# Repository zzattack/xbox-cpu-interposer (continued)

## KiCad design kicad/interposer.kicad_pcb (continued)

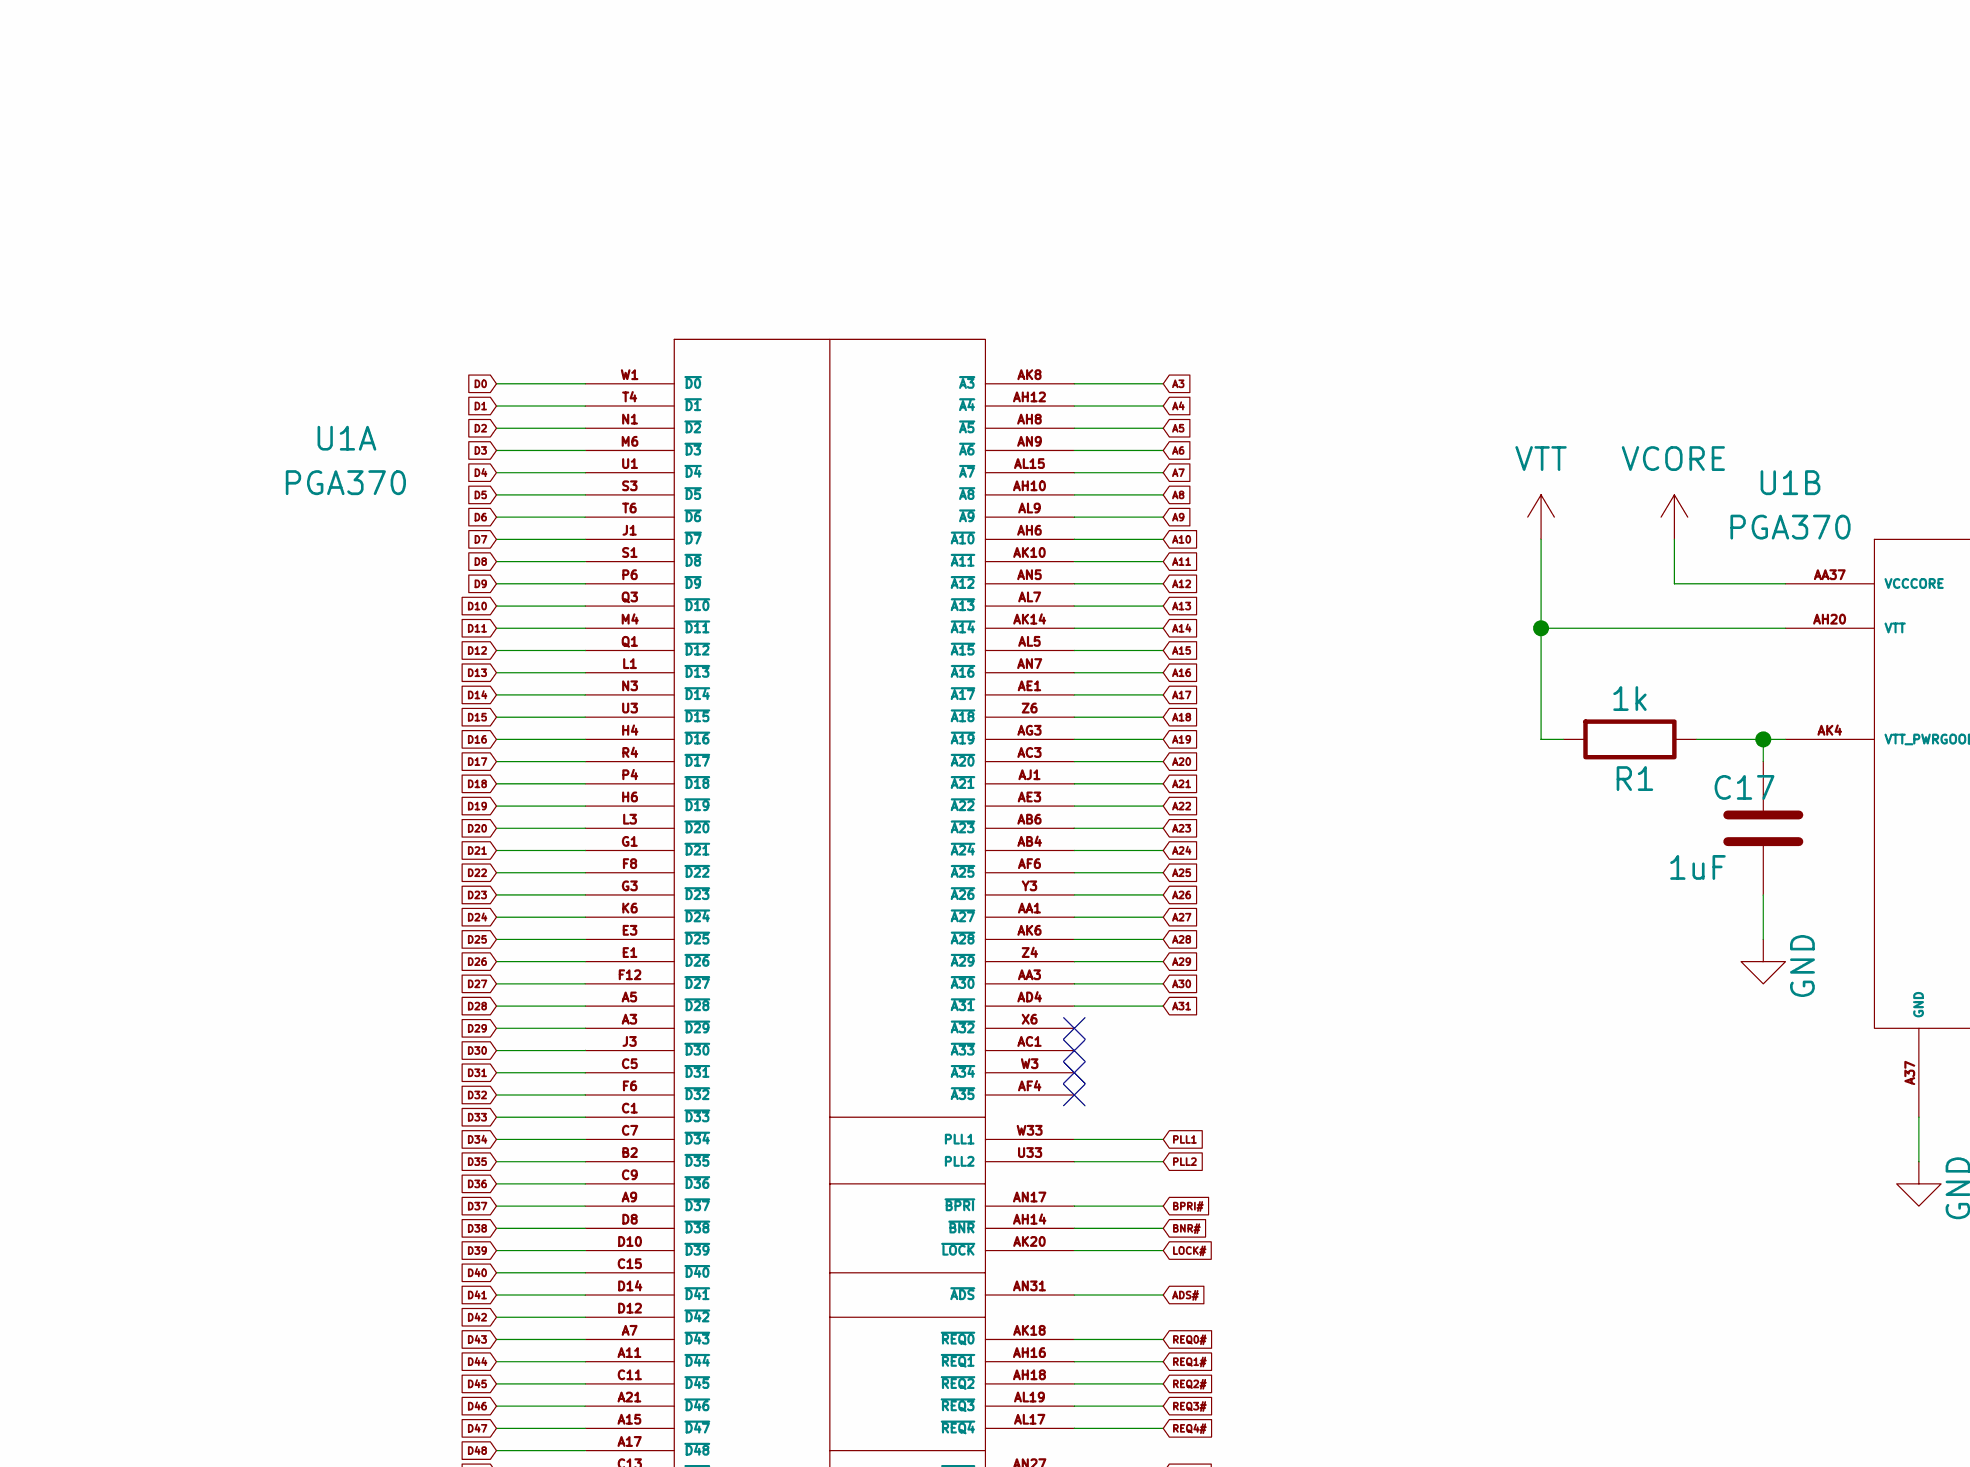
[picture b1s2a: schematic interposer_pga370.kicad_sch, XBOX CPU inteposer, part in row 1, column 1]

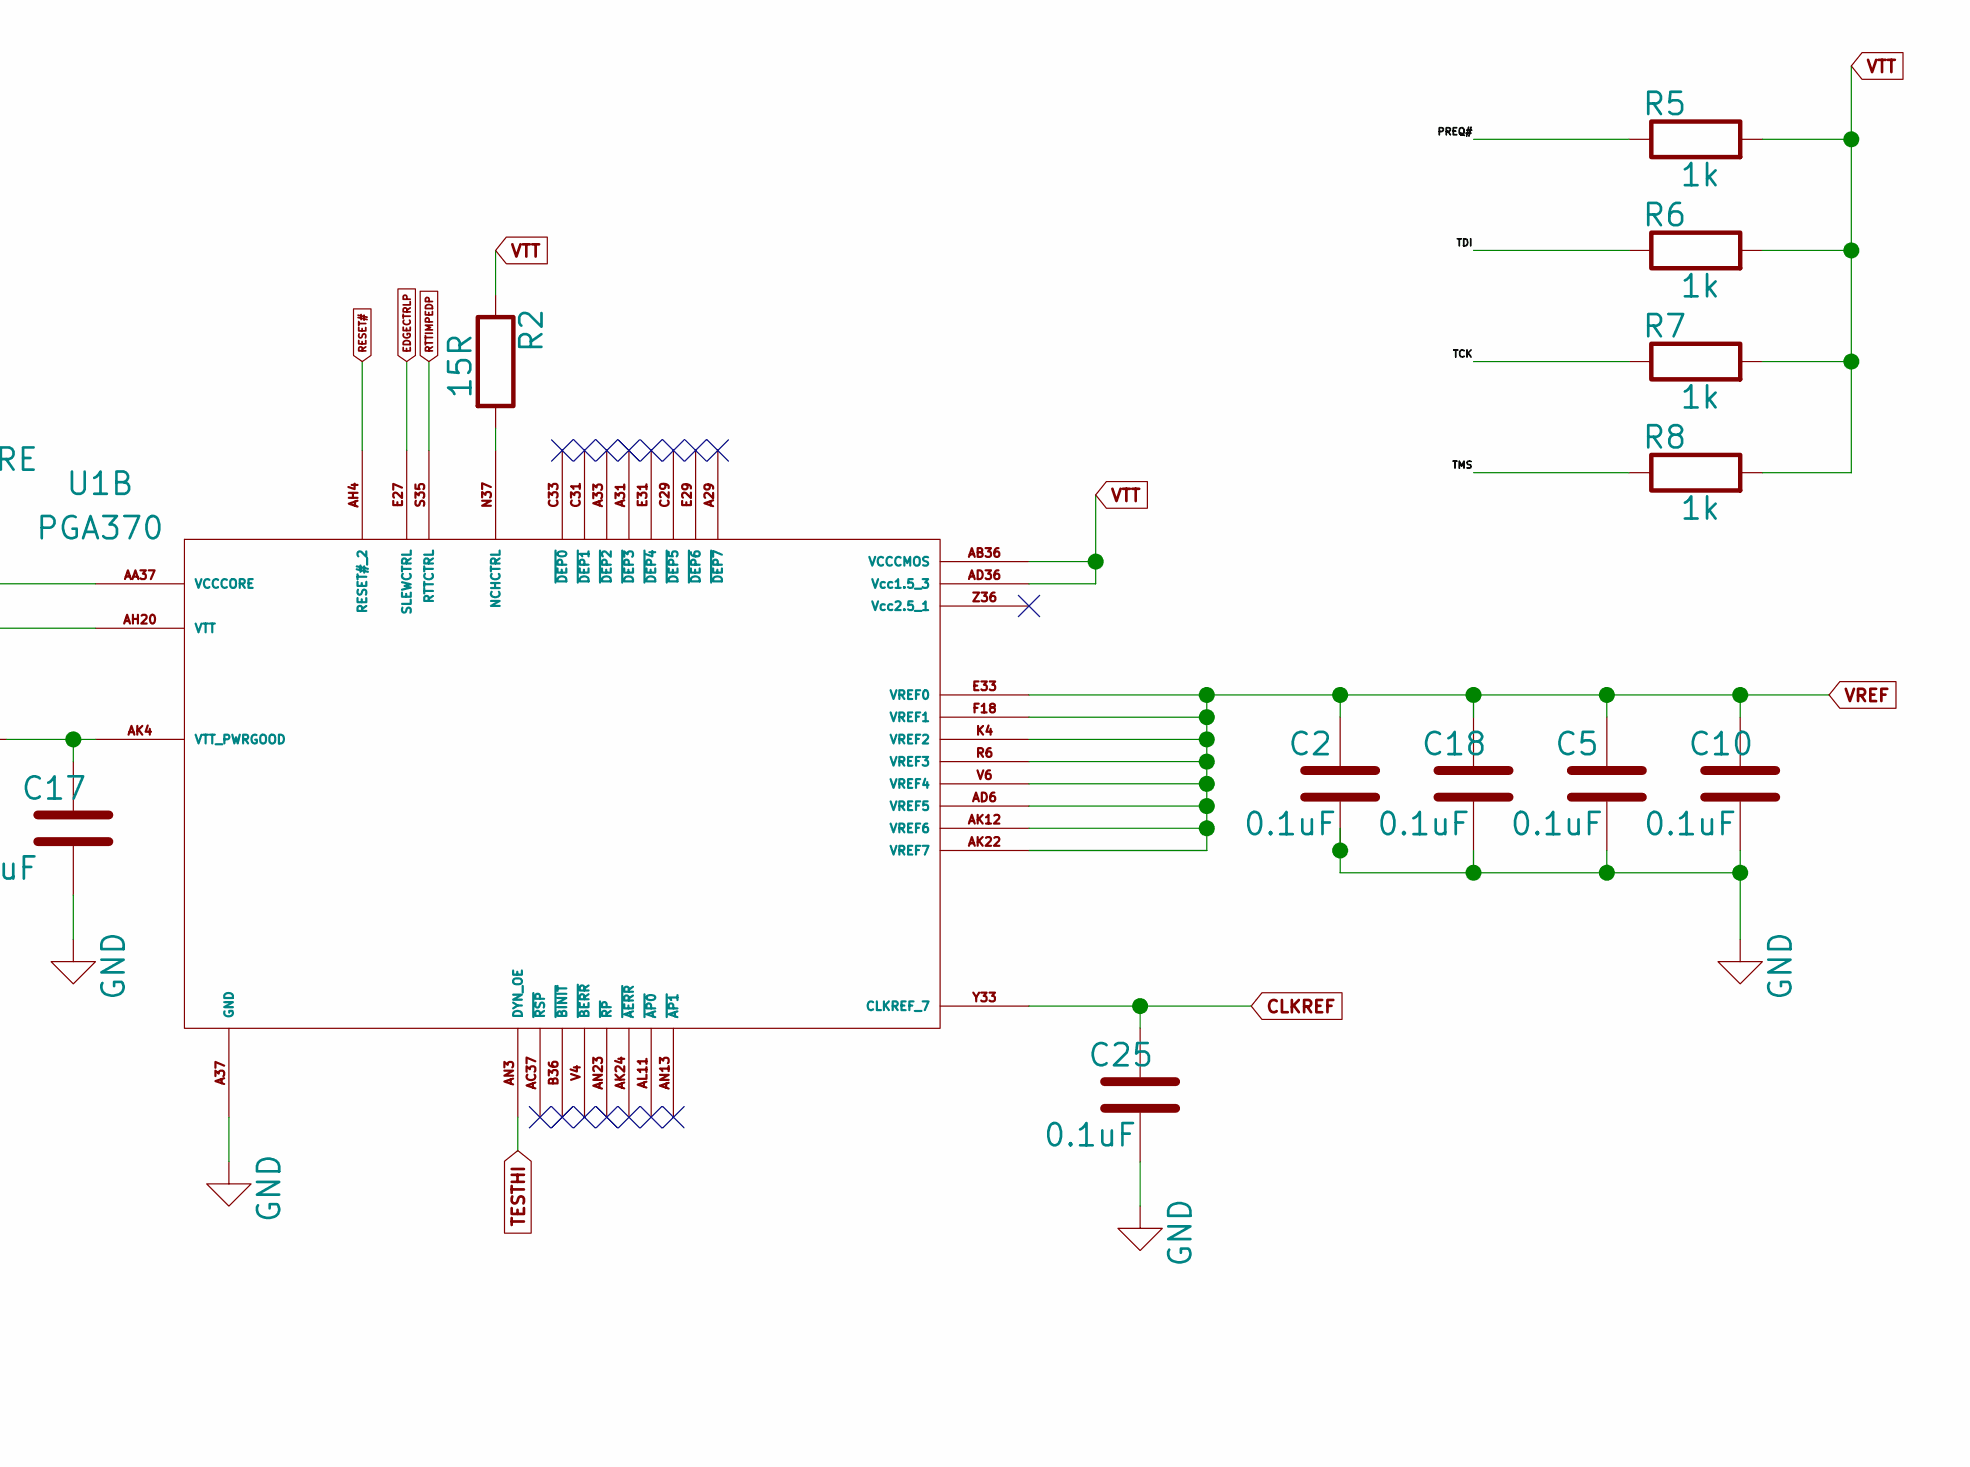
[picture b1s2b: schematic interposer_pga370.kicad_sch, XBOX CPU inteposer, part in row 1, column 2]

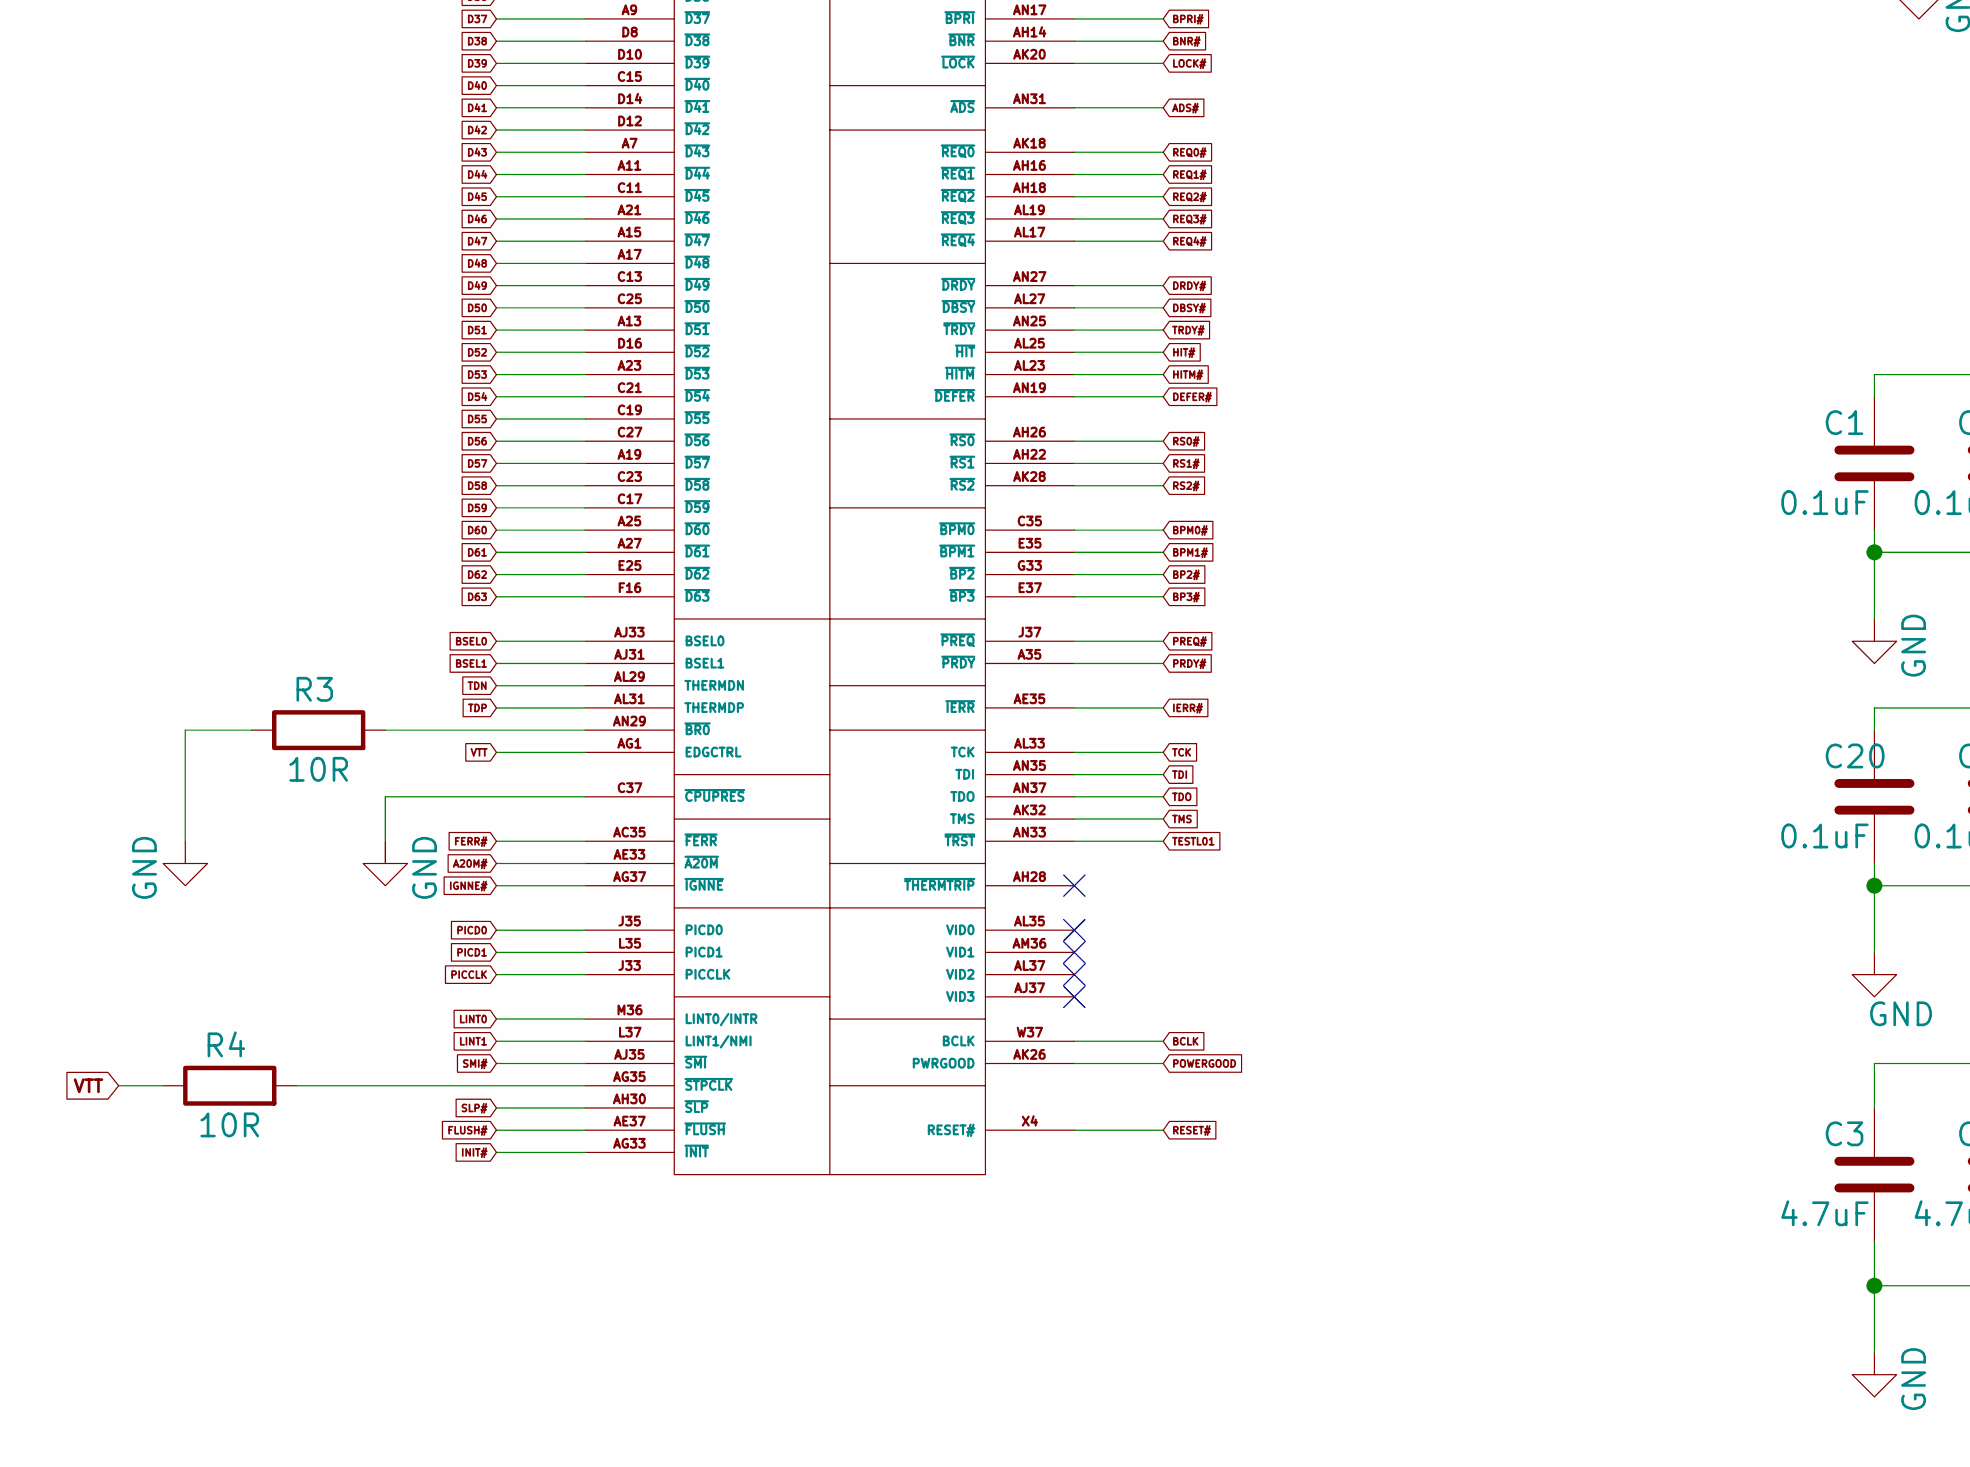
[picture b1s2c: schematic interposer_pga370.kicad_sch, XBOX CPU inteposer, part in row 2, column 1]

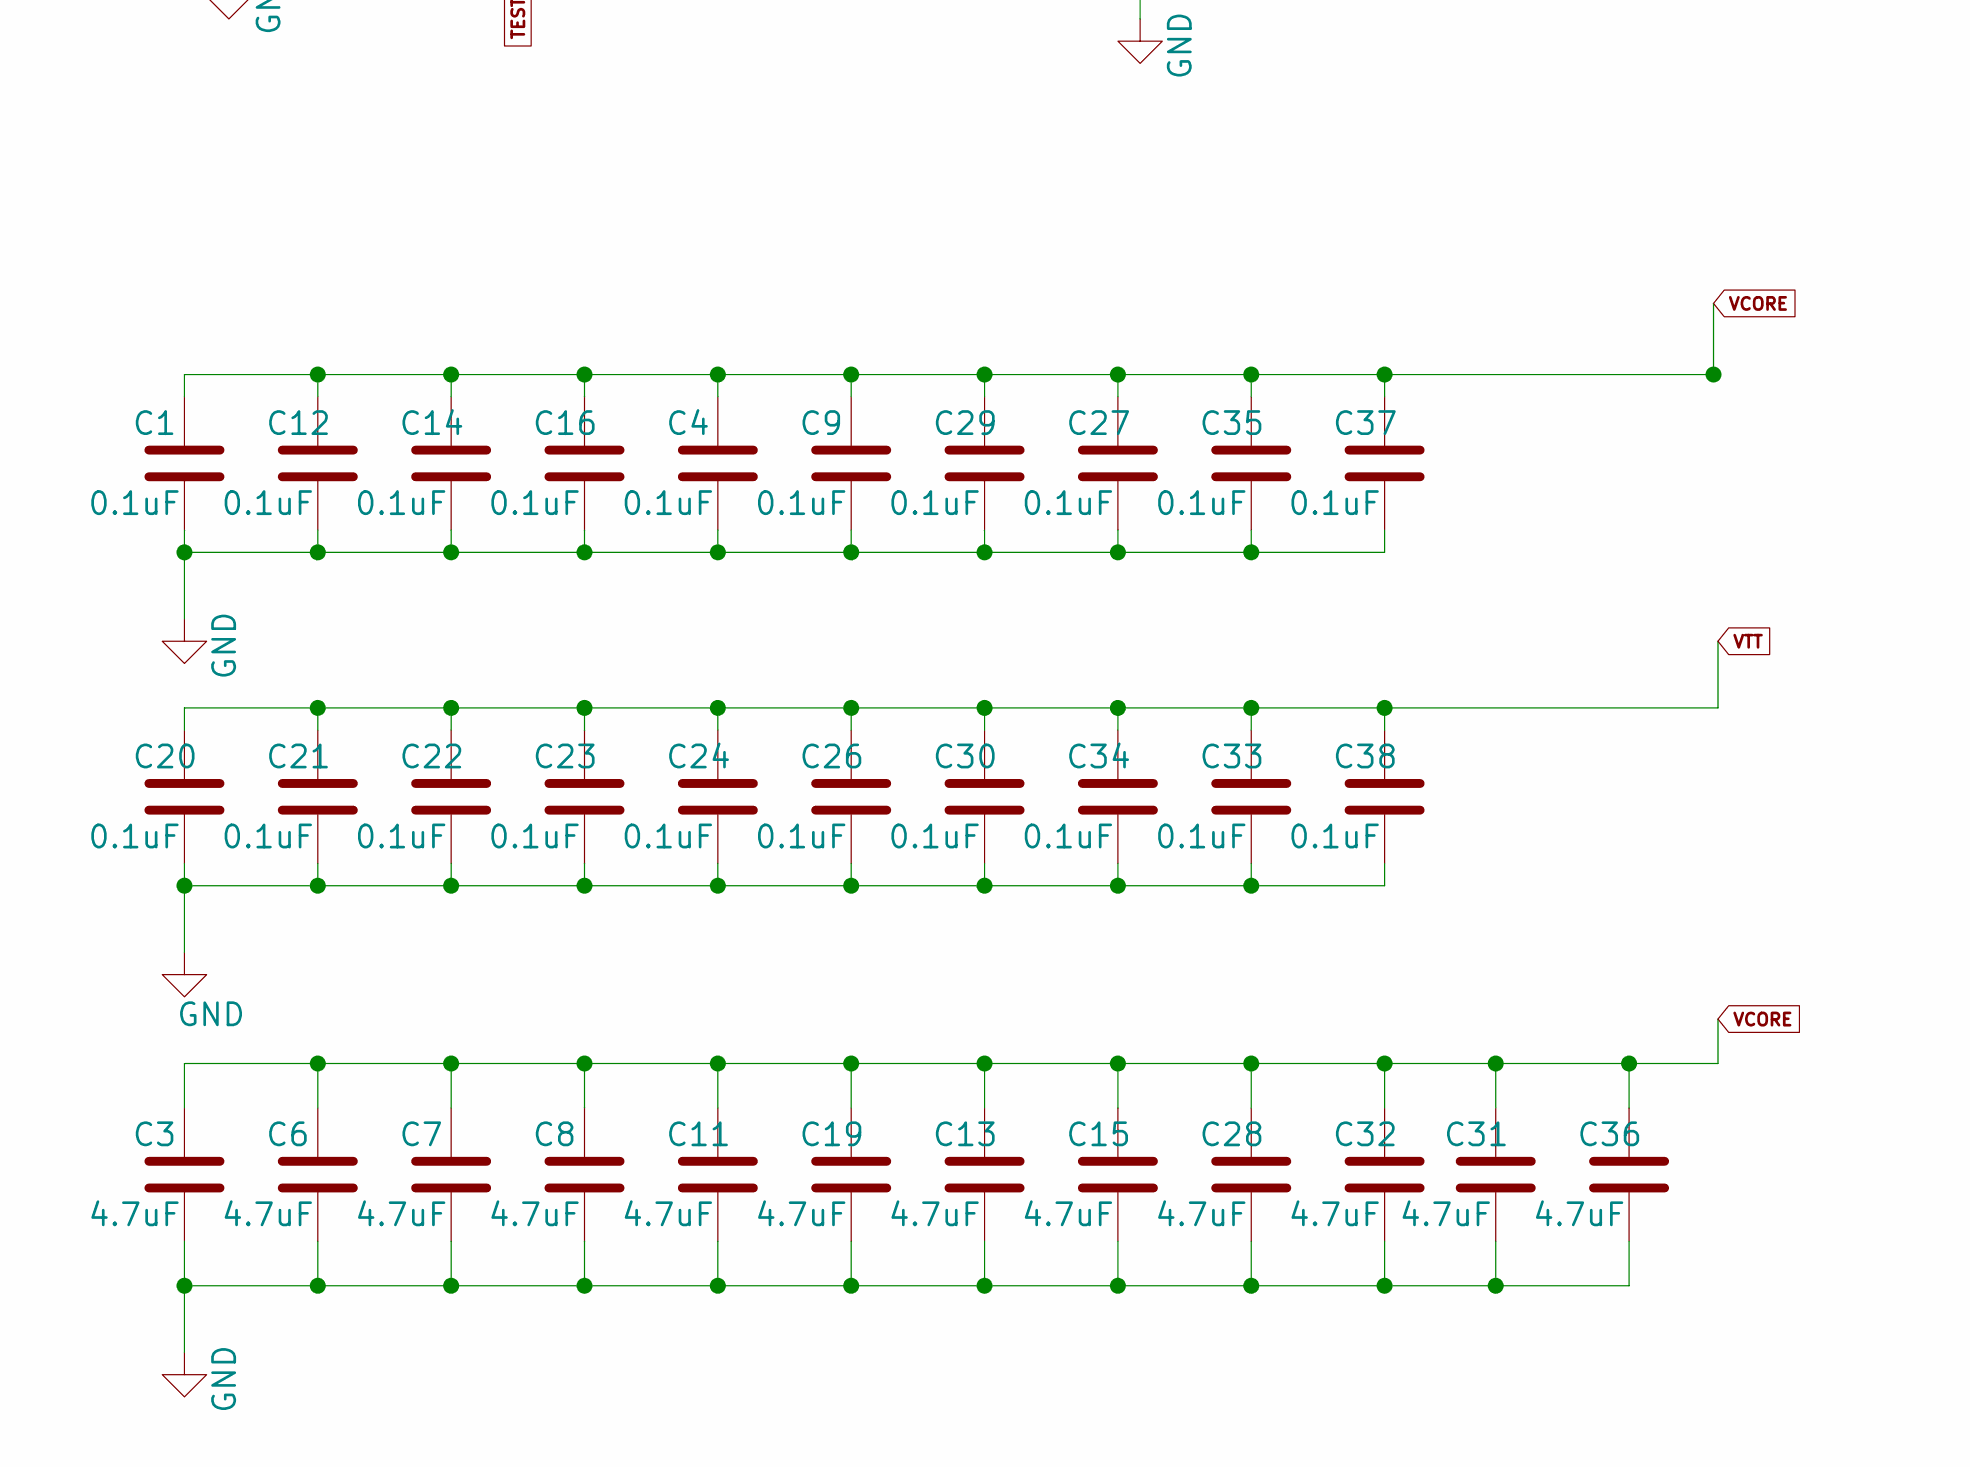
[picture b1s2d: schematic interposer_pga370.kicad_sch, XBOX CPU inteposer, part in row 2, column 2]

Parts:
C1, C2, C4, C5, C9, C10, C12, C14, C16, C18, C20, C21, C22, C23, C24, C25, C26, C27, C29, C30, C33, C34, C35, C37, C38: 0.1uF; C_0603_1608Metric
C3, C6, C7, C8, C11, C13, C15, C19, C28, C31, C32, C36: 4.7uF; C_0805_2012Metric
C17: 1uF; C_0603_1608Metric
R1, R5, R6, R7, R8: 1k; R_0603_1608Metric
R2: 15R; R_0603_1608Metric
R3, R4: 10R; R_0603_1608Metric
U1: PGA370

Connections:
A3: U1.AK8 (~A3); also elsewhere on the board
A4: U1.AH12 (~A4); also elsewhere on the board
A5: U1.AH8 (~A5); also elsewhere on the board
A6: U1.AN9 (~A6); also elsewhere on the board
A7: U1.AL15 (~A7); also elsewhere on the board
A8: U1.AH10 (~A8); also elsewhere on the board
A9: U1.AL9 (~A9); also elsewhere on the board
A10: U1.AH6 (~A10); also elsewhere on the board
A11: U1.AK10 (~A11); also elsewhere on the board
A12: U1.AN5 (~A12); also elsewhere on the board
A13: U1.AL7 (~A13); also elsewhere on the board
A14: U1.AK14 (~A14); also elsewhere on the board
A15: U1.AL5 (~A15); also elsewhere on the board
A16: U1.AN7 (~A16); also elsewhere on the board
A17: U1.AE1 (~A17); also elsewhere on the board
A18: U1.Z6 (~A18); also elsewhere on the board
A19: U1.AG3 (~A19); also elsewhere on the board
A20: U1.AC3 (~A20); also elsewhere on the board
A20M#: U1.AE33 (~A20M); also elsewhere on the board
A21: U1.AJ1 (~A21); also elsewhere on the board
A22: U1.AE3 (~A22); also elsewhere on the board
A23: U1.AB6 (~A23); also elsewhere on the board
A24: U1.AB4 (~A24); also elsewhere on the board
A25: U1.AF6 (~A25); also elsewhere on the board
A26: U1.Y3 (~A26); also elsewhere on the board
A27: U1.AA1 (~A27); also elsewhere on the board
A28: U1.AK6 (~A28); also elsewhere on the board
A29: U1.Z4 (~A29); also elsewhere on the board
A30: U1.AA3 (~A30); also elsewhere on the board
A31: U1.AD4 (~A31); also elsewhere on the board
ADS#: U1.AN31 (~ADS); also elsewhere on the board
BCLK: U1.W37 (BCLK); also elsewhere on the board
BNR#: U1.AH14 (~BNR); also elsewhere on the board
BP2#: U1.G33 (~BP2); also elsewhere on the board
BP3#: U1.E37 (~BP3); also elsewhere on the board
BPM0#: U1.C35 (~BPM0); also elsewhere on the board
BPM1#: U1.E35 (~BPM1); also elsewhere on the board
BPRI#: U1.AN17 (~BPRI); also elsewhere on the board
BSEL0: U1.AJ33 (BSEL0); also elsewhere on the board
BSEL1: U1.AJ31 (BSEL1); also elsewhere on the board
CLKREF: C25.1, U1.Y33 (CLKREF_7); also elsewhere on the board
D0: U1.W1 (~D0); also elsewhere on the board
D1: U1.T4 (~D1); also elsewhere on the board
D2: U1.N1 (~D2); also elsewhere on the board
D3: U1.M6 (~D3); also elsewhere on the board
D4: U1.U1 (~D4); also elsewhere on the board
D5: U1.S3 (~D5); also elsewhere on the board
D6: U1.T6 (~D6); also elsewhere on the board
D7: U1.J1 (~D7); also elsewhere on the board
D8: U1.S1 (~D8); also elsewhere on the board
D9: U1.P6 (~D9); also elsewhere on the board
D10: U1.Q3 (~D10); also elsewhere on the board
D11: U1.M4 (~D11); also elsewhere on the board
D12: U1.Q1 (~D12); also elsewhere on the board
D13: U1.L1 (~D13); also elsewhere on the board
D14: U1.N3 (~D14); also elsewhere on the board
D15: U1.U3 (~D15); also elsewhere on the board
D16: U1.H4 (~D16); also elsewhere on the board
D17: U1.R4 (~D17); also elsewhere on the board
D18: U1.P4 (~D18); also elsewhere on the board
D19: U1.H6 (~D19); also elsewhere on the board
D20: U1.L3 (~D20); also elsewhere on the board
D21: U1.G1 (~D21); also elsewhere on the board
D22: U1.F8 (~D22); also elsewhere on the board
D23: U1.G3 (~D23); also elsewhere on the board
D24: U1.K6 (~D24); also elsewhere on the board
D25: U1.E3 (~D25); also elsewhere on the board
D26: U1.E1 (~D26); also elsewhere on the board
D27: U1.F12 (~D27); also elsewhere on the board
D28: U1.A5 (~D28); also elsewhere on the board
D29: U1.A3 (~D29); also elsewhere on the board
D30: U1.J3 (~D30); also elsewhere on the board
D31: U1.C5 (~D31); also elsewhere on the board
D32: U1.F6 (~D32); also elsewhere on the board
D33: U1.C1 (~D33); also elsewhere on the board
D34: U1.C7 (~D34); also elsewhere on the board
D35: U1.B2 (~D35); also elsewhere on the board
D36: U1.C9 (~D36); also elsewhere on the board
D37: U1.A9 (~D37); also elsewhere on the board
D38: U1.D8 (~D38); also elsewhere on the board
D39: U1.D10 (~D39); also elsewhere on the board
D40: U1.C15 (~D40); also elsewhere on the board
D41: U1.D14 (~D41); also elsewhere on the board
D42: U1.D12 (~D42); also elsewhere on the board
D43: U1.A7 (~D43); also elsewhere on the board
D44: U1.A11 (~D44); also elsewhere on the board
D45: U1.C11 (~D45); also elsewhere on the board
D46: U1.A21 (~D46); also elsewhere on the board
D47: U1.A15 (~D47); also elsewhere on the board
D48: U1.A17 (~D48); also elsewhere on the board
D49: U1.C13 (~D49); also elsewhere on the board
D50: U1.C25 (~D50); also elsewhere on the board
D51: U1.A13 (~D51); also elsewhere on the board
D52: U1.D16 (~D52); also elsewhere on the board
D53: U1.A23 (~D53); also elsewhere on the board
D54: U1.C21 (~D54); also elsewhere on the board
D55: U1.C19 (~D55); also elsewhere on the board
D56: U1.C27 (~D56); also elsewhere on the board
D57: U1.A19 (~D57); also elsewhere on the board
D58: U1.C23 (~D58); also elsewhere on the board
D59: U1.C17 (~D59); also elsewhere on the board
D60: U1.A25 (~D60); also elsewhere on the board
D61: U1.A27 (~D61); also elsewhere on the board
D62: U1.E25 (~D62); also elsewhere on the board
D63: U1.F16 (~D63); also elsewhere on the board
DBSY#: U1.AL27 (~DBSY); also elsewhere on the board
DEFER#: U1.AN19 (~DEFER); also elsewhere on the board
DRDY#: U1.AN27 (~DRDY); also elsewhere on the board
EDGECTRLP: U1.E27 (SLEWCTRL); also elsewhere on the board
FERR#: U1.AC35 (~FERR); also elsewhere on the board
FLUSH#: U1.AE37 (~FLUSH); also elsewhere on the board
GND: C1.2, C2.2, C3.2, C4.2, C5.2, C6.2, C7.2, C8.2, C9.2, C10.2, C11.2, C12.2, C13.2, C14.2, C15.2, C16.2, C17.2, C18.2, C19.2, C20.2, C21.2, C22.2, C23.2, C24.2, C25.2, C26.2, C27.2, C28.2, C29.2, C30.2, C31.2, C32.2, C33.2, C34.2, C35.2, C36.2, C37.2, C38.2, R3.1, U1.A37 (GND), U1.AB32 (GND), U1.AC5 (GND), U1.AC33 (GND), U1.AD2 (GND), U1.AD34 (GND), U1.AF32 (GND), U1.AG5 (GND), U1.AH2 (GND), U1.AH34 (GND), U1.AJ7 (GND), U1.AJ11 (GND), U1.AJ15 (GND), U1.AJ19 (GND), U1.AJ23 (GND), U1.AJ27 (GND), U1.AL3 (GND), U1.AM6 (GND), U1.AM10 (GND), U1.AM14 (GND), U1.AM18 (GND), U1.AM22 (GND), U1.AM26 (GND), U1.AM30 (GND), U1.AM34 (GND), U1.B4 (GND), U1.B8 (GND), U1.B12 (GND), U1.B16 (GND), U1.B20 (GND), U1.B24 (GND), U1.B28 (GND), U1.B32 (GND), U1.C37 (~CPUPRES), U1.D2 (GND), U1.D4 (GND), U1.D18 (GND), U1.D22 (GND), U1.D26 (GND), U1.D30 (GND), U1.D34 (GND), U1.E7 (GND), U1.E11 (GND), U1.E15 (GND), U1.E19 (GND), U1.F20 (GND), U1.F24 (GND), U1.F28 (GND), U1.F32 (GND), U1.F36 (GND), U1.G5 (GND), U1.H2 (GND), U1.H34 (GND), U1.K36 (GND), U1.L5 (GND), U1.M2 (GND), U1.M34 (GND), U1.P32 (GND), U1.P36 (GND), U1.Q5 (GND), U1.R34 (GND), U1.T32 (GND), U1.T36 (GND), U1.U5 (GND), U1.V2 (GND), U1.V34 (GND), U1.X32 (GND), U1.X36 (GND), U1.Y5 (GND), U1.Y37 (GND), U1.Z2 (GND), U1.Z34 (GND); also elsewhere on the board
HIT#: U1.AL25 (~HIT); also elsewhere on the board
HITM#: U1.AL23 (~HITM); also elsewhere on the board
IERR#: U1.AE35 (~IERR); also elsewhere on the board
IGNNE#: U1.AG37 (~IGNNE); also elsewhere on the board
INIT#: U1.AG33 (~INIT); also elsewhere on the board
LINT0: U1.M36 (LINT0/INTR); also elsewhere on the board
LINT1: U1.L37 (LINT1/NMI); also elsewhere on the board
LOCK#: U1.AK20 (~LOCK); also elsewhere on the board
unnamed: R3.2, U1.AN29 (~BR0)
unnamed: R4.2, U1.AG35 (~STPCLK)
unnamed: R2.2, U1.N37 (NCHCTRL)
unnamed: C17.1, R1.1, U1.AK4 (VTT_PWRGOOD)
PICCLK: U1.J33 (PICCLK); also elsewhere on the board
PICD0: U1.J35 (PICD0); also elsewhere on the board
PICD1: U1.L35 (PICD1); also elsewhere on the board
PLL1: U1.W33 (PLL1); also elsewhere on the board
PLL2: U1.U33 (PLL2); also elsewhere on the board
POWERGOOD: U1.AK26 (PWRGOOD); also elsewhere on the board
PRDY#: U1.A35 (~PRDY); also elsewhere on the board
PREQ#: R5.1, U1.J37 (~PREQ)
REQ0#: U1.AK18 (~REQ0); also elsewhere on the board
REQ1#: U1.AH16 (~REQ1); also elsewhere on the board
REQ2#: U1.AH18 (~REQ2); also elsewhere on the board
REQ3#: U1.AL19 (~REQ3); also elsewhere on the board
REQ4#: U1.AL17 (~REQ4); also elsewhere on the board
RESET#: U1.AH4 (RESET#_2), U1.X4 (RESET#); also elsewhere on the board
RS0#: U1.AH26 (~RS0); also elsewhere on the board
RS1#: U1.AH22 (~RS1); also elsewhere on the board
RS2#: U1.AK28 (~RS2); also elsewhere on the board
RTTIMPEDP: U1.S35 (RTTCTRL); also elsewhere on the board
SLP#: U1.AH30 (~SLP); also elsewhere on the board
SMI#: U1.AJ35 (~SMI); also elsewhere on the board
TCK: R7.1, U1.AL33 (TCK)
TDI: R6.1, U1.AN35 (TDI)
TDN: U1.AL29 (THERMDN); also elsewhere on the board
TDO: U1.AN37 (TDO); also elsewhere on the board
TDP: U1.AL31 (THERMDP); also elsewhere on the board
TESTHI: U1.AN3 (DYN_OE); also elsewhere on the board
TESTL01: U1.AN33 (~TRST); also elsewhere on the board
TMS: R8.1, U1.AK32 (TMS)
TRDY#: U1.AN25 (~TRDY); also elsewhere on the board
VCORE: C1.1, C3.1, C4.1, C6.1, C7.1, C8.1, C9.1, C11.1, C12.1, C13.1, C14.1, C15.1, C16.1, C19.1, C27.1, C28.1, C29.1, C31.1, C32.1, C35.1, C36.1, C37.1, U1.AA5 (VCORE), U1.AA37 (VCCCORE), U1.AB2 (VCORE), U1.AB34 (VCORE), U1.AD32 (VCORE), U1.AE5 (VCORE), U1.AF2 (VCORE), U1.AF34 (VCORE), U1.AH24 (VCORE), U1.AH32 (VCORE), U1.AH36 (VCORE), U1.AJ5 (VCORE), U1.AJ9 (VCORE), U1.AJ13 (VCORE), U1.AJ17 (VCORE), U1.AJ21 (VCORE), U1.AJ25 (VCORE), U1.AJ29 (VCORE), U1.AK2 (VCORE), U1.AK34 (VCORE), U1.AM4 (VCORE), U1.AM8 (VCORE), U1.AM12 (VCORE), U1.AM16 (VCORE), U1.AM20 (VCORE), U1.AM24 (VCORE), U1.AM28 (VCORE), U1.AM32 (VCORE), U1.B6 (VCORE), U1.B10 (VCORE), U1.B14 (VCORE), U1.B18 (VCORE), U1.B22 (VCORE), U1.B26 (VCORE), U1.B30 (VCORE), U1.B34 (VCORE), U1.C3 (VCORE), U1.D6 (VCORE), U1.D20 (VCORE), U1.D24 (VCORE), U1.D28 (VCORE), U1.D32 (VCORE), U1.D36 (VCORE), U1.E5 (VCORE), U1.E9 (VCORE), U1.E13 (VCORE), U1.E17 (VCORE), U1.F2 (VCORE), U1.F4 (VCORE), U1.F14 (VCORE), U1.F22 (VCORE), U1.F26 (VCORE), U1.F30 (VCORE), U1.F34 (VCORE), U1.H32 (VCORE), U1.H36 (VCORE), U1.J5 (VCORE), U1.K2 (VCORE), U1.K32 (VCORE), U1.K34 (VCORE), U1.M32 (VCORE), U1.N5 (VCORE), U1.P2 (VCORE), U1.P34 (VCORE), U1.R32 (VCORE), U1.R36 (VCORE), U1.S5 (VCORE), U1.T2 (VCORE), U1.T34 (VCORE), U1.V32 (VCORE), U1.V36 (VCORE), U1.W5 (VCORE), U1.Y35 (VCORE), U1.Z32 (VCORE); also elsewhere on the board
VREF: C2.1, C5.1, C10.1, C18.1, U1.AD6 (VREF5), U1.AK12 (VREF6), U1.AK22 (VREF7), U1.E33 (VREF0), U1.F18 (VREF1), U1.K4 (VREF2), U1.R6 (VREF3), U1.V6 (VREF4); also elsewhere on the board
VTT: C20.1, C21.1, C22.1, C23.1, C24.1, C26.1, C30.1, C33.1, C34.1, C38.1, R1.2, R2.1, R4.1, R5.2, R6.2, R7.2, R8.2, U1.AA33 (VTT), U1.AA35 (VTT), U1.AB36 (VCCCMOS), U1.AD36 (Vcc1.5_3), U1.AG1 (EDGCTRL), U1.AH20 (VTT), U1.AK16 (VTT), U1.AL13 (VTT), U1.AL21 (VTT), U1.AN11 (VTT), U1.AN15 (VTT), U1.AN21 (VTT), U1.E23 (VTT), U1.G35 (VTT), U1.G37 (VTT), U1.S33 (VTT), U1.S37 (VTT), U1.U35 (VTT), U1.U37 (VTT), U1.X34 (VTT); also elsewhere on the board

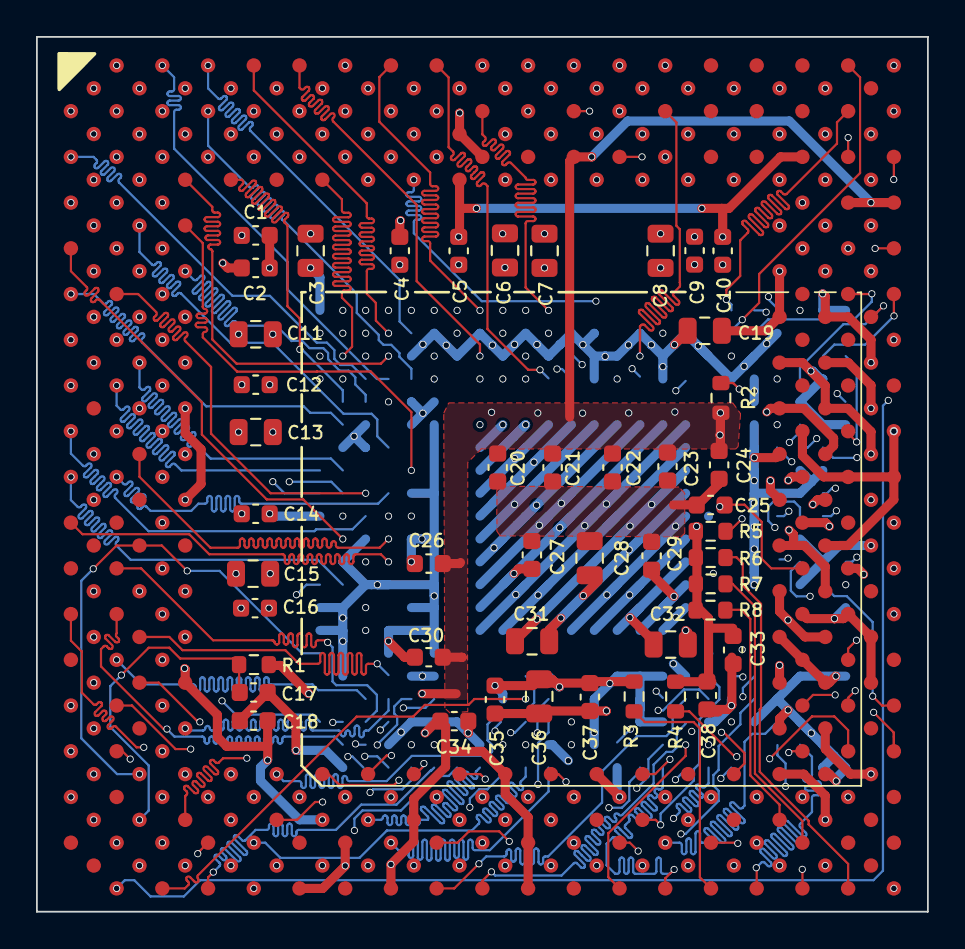
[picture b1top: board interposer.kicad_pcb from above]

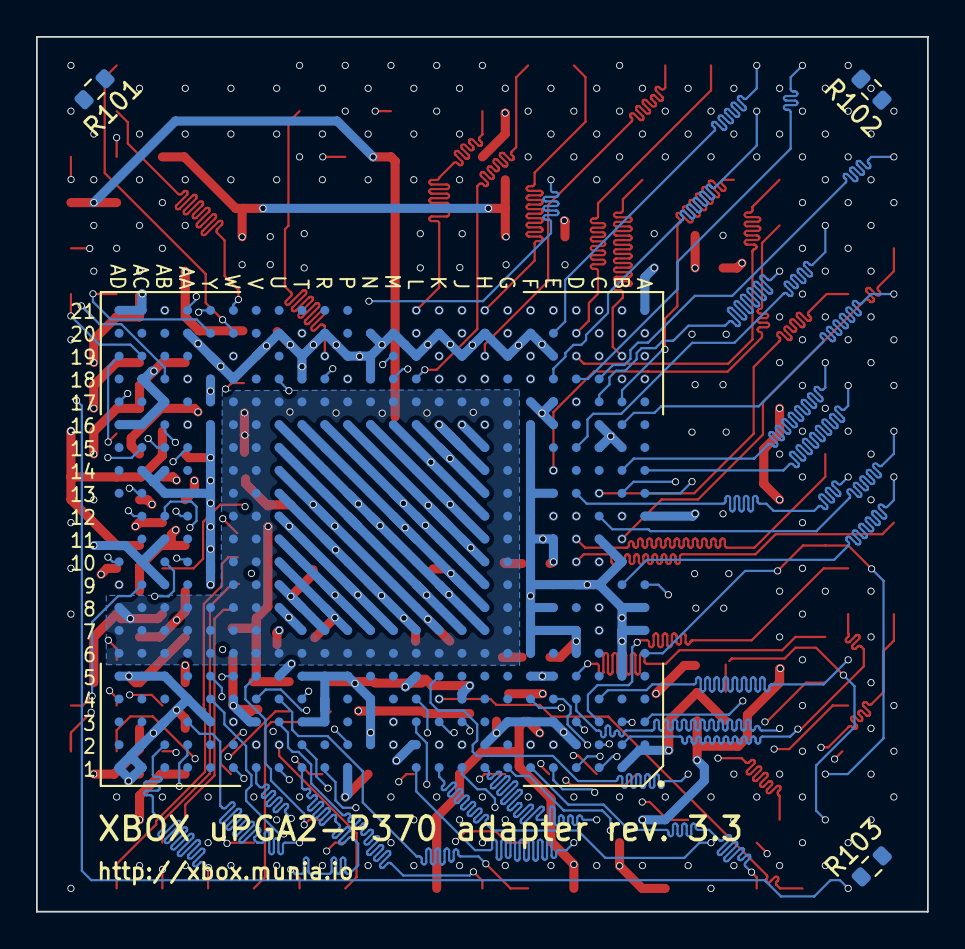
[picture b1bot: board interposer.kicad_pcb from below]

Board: 6 copper layers, 49.5 x 48.6 mm, 51 parts (4 on the bottom side), 156 nets.

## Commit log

2023-11-26 Add aligned and cleaned-up scans of delayered board
2023-11-26 Add datasheets for the source and target processor families
2023-11-26 Add kicad project with sch, symbols, footprints and pcb
2023-11-26 Add friendtech patent
2023-11-28 Reroute with BGA more centered and cheaper design fabrications (0.3mm drills).
2023-11-28 Remove license
2023-11-29 Optimizations: - remove via's out of silk screen text - eliminate warnings - tighter board outline
2023-12-01 Revision 3; much cleaner layout with traces tuned to 25mm.
2023-12-01 Add tool to help with alignment of the board
2023-12-01 Add gerbers for aligntool
2023-12-08 Rev 3.1: - change via's to 0.3mm drill/0.4mm ring for cheaper manufacturing - add leveling 0603 resistors on backside in the corners to prevent PCB tilt during reflow
2024-01-07 Revision 3.2
    Implement fixes that allow interposer to be actually functional for the first time:
    - Fix uBGA495 pin P1 from VTT --> VCC since this is VCC on xbox motherboard.
    - Fix P370 pin AJ3 (RESET2#) from GND --> NC.
    Furthermore, pins AL1 (reserved), AK36 (VID output), AF36 (DETECT) now left NC instead of connected to GND.
    Outline slightly trimmed near bottom to provide some clearance against a cap on 1.6 motherboards.
    Design specs loosened, from 4 mil tracks/4 mil clearance/0.3mm drills --> 5 mil/5 mil/0.3mm.
2024-01-07 Update BOM
2024-01-21 Add stencils
2024-08-14 Rev. 3.3, minor changes: - Resistor network RN01 changed to 4 distinct 0603's since people continuously order an incorrect part - Height of interposer slightly reduced by 0.3mm on both top and bottom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
2025-02-01 Create guide
2026-05-24 Spelling stuff
